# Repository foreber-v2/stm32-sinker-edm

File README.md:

# stm32-sinker-edm

# Open-Source Low-Cost Sinker EDM (STM32)

<p align="center">
  
</p>

<div align="center" style="text-align:center;">
  
  <br>
  <em>📱 Watch the full YouTube Short demo</em>
</div>

<br>

An ultra-low-cost, open-source Sinker Electrical Discharge Machining (EDM) prototype designed to make advanced subtractive manufacturing accessible. Built using mostly recycled components and standard locally-sourced parts.

---

## 🎥 Demo & Working Principle

<h2 align="center" style="text-align:center; border:none;">🎥 Demonstration & Results</h2>

<!-- FILA 1: VIDEOS -->
<table align="center" border="0" cellspacing="0" cellpadding="10" style="display:table; width:auto; margin:0 auto; border:none;">
  <tr>
    <td align="center" valign="bottom" style="text-align:center; border:none; background:none;">
      <b>📺 Full Demo</b><br>
      
    </td>
    <td align="center" valign="bottom" style="text-align:center; border:none; background:none;">
      <b>📱 Short Demo</b><br>
      
    </td>
  </tr>
</table>

<!-- FILA 2: FOTOS (ahora clicables, abren la imagen completa) -->
<table align="center" border="0" cellspacing="0" cellpadding="10" style="display:table; width:auto; margin:0 auto; border:none;">
  <tr>
    <td align="center" valign="top" style="text-align:center; border:none; background:none;">
      
      <br>
      <sub><i>Fig 1. Workpieces detail</i></sub>
    </td>
    <td align="center" valign="top" style="text-align:center; border:none; background:none;">
      
      <br>
      <sub><i>Fig 2. Surface finish</i></sub>
    </td>
  </tr>
</table>

---

## 📌 A. Project Overview

### What problem does it solve?
Advanced subtractive manufacturing—specifically Electrical Discharge Machining (EDM)—is traditionally prohibitively expensive, limiting access to high-precision hard-metal cutting in low-income regions, small workshops, and educational environments. This project tackles that barrier by creating an open-source, ultra-low-cost sinker EDM machine built from the ground up using mostly recycled and locally available components.

### What was built?
A complete prototype system consisting of:
* A custom **spark-generating power unit** handling up to 150VDC and delivering adjustable pulses up to ~40A.
* Real-time **pulse monitoring and sensing** using LM311 comparators, keeping a tight 60 µs pulse width (establishing a theoretical 16.6 kHz frequency ceiling).
* A mechanical linear axis driven by standard **NEMA 17 stepper motors** to control electrode feed.
* An **STM32 microcontroller** core running refactored, English-documented firmware.

### Current development status
* **Status:** Experimental prototype ("As-Is").
* **Testing Note:** The control logic has been refactored, but it must be rigorously tested dry (without high-voltage rails or high-power IGBT stages) before live deployment.
* **Philosophy:** *It cuts indeed.*

---

## 📑 Documentation Index

Explore the detailed technical documentation for each subsystem below:

* **[B. System Architecture](docs/architecture.md)** — Block diagrams, power electronics topology, control loop logic, and user interface layout.
* **[C. Hardware & Bill of Materials](docs/hardware.md)** — recycled component sourcing, and physical assembly insides.
* **[D. Firmware & Control Logic](docs/control.md)** — Keil uVision project structure, state machines, pulse-monitoring routines, and safety/fault handling.
* **[E. Experimental Results & Oscilloscope Captures](docs/experimental-results.md) (Coming Soon)** — Short/open-circuit waveforms, gate drive signals, current noise analysis, cutting tests, and limitations.
* **[F. Engineering Decisions & Trade-offs](docs/engineering-decisions.md) (Coming Soon)** — Sinker vs. Wire EDM choice, reusing telecom power supplies (-50VDC), opting for IGBTs with built-in flyback diodes, method of short/spark detection, and cost optimization.
* **[G. Future Improvements](docs/future-improvements.md) (Coming Soon)** — Fluid flushing systems, advanced instrumentation, closed-loop actuator speed optimization, and next-gen roadmap.

---

<p align="center">
  <a href="#stm32-sinker-edm">⬆️ Back to Top</a>
</p>

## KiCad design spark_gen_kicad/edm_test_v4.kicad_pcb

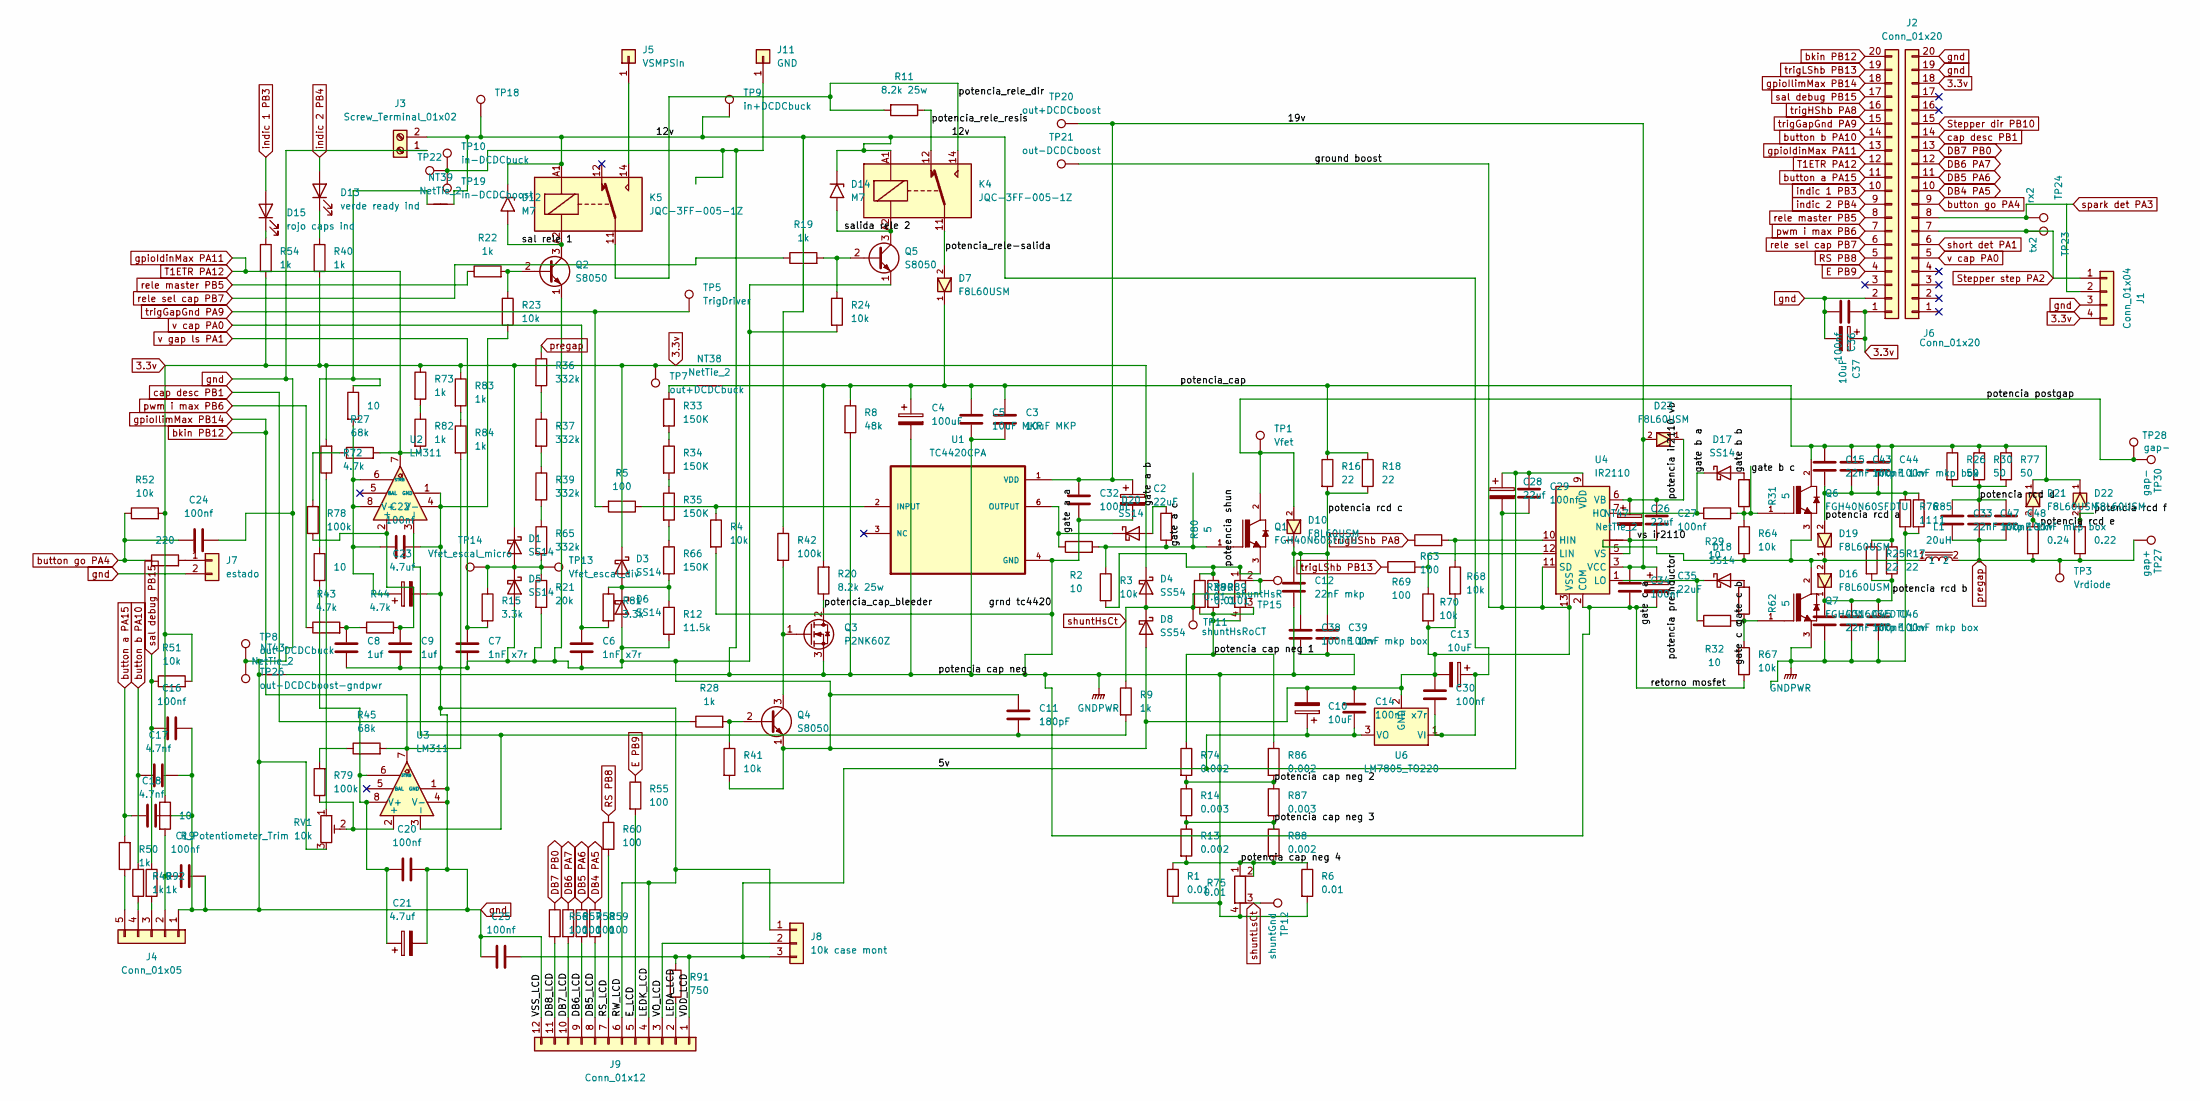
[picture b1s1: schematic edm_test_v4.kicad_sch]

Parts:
C2, C35: 22uF; CP_Radial_D5.0mm_P2.00mm
C3, C5: 10uF MKP; CP_Axial_L38.0mm_D21.0mm_P44.00mm_Horizontal
C4: 100uF; CP_Radial_D14.0mm_P7.50mm
C6, C7: 1nF x7r; C_Disc_D10.5mm_W5.0mm_P7.50mm
C8, C9: 1uf; C_1206_3216Metric_Pad1.33x1.80mm_HandSolder
C10, C13: 10uF; CP_Radial_D5.0mm_P2.50mm
C11: 180pF; C_Disc_D3.4mm_W2.1mm_P2.50mm
C12, C15, C31, C33: 22nF mkp; CP_Axial_L11.0mm_D6.0mm_P18.00mm_Horizontal
C14: 100nF x7r; C_0603_1608Metric_Pad1.08x0.95mm_HandSolder
C16, C19, C20, C22, C24, C25, C27, C29, C30, C32, C34, C36: 100nf; C_0603_1608Metric_Pad1.08x0.95mm_HandSolder
C17, C18: 4.7nf; C_0603_1608Metric_Pad1.08x0.95mm_HandSolder
C21, C23: 4.7uf; CP_Radial_D5.0mm_P2.50mm
C26, C28: 22uf; CP_Radial_D5.0mm_P2.50mm
C37: 10uF; CP_Radial_D5.0mm_P2.00mm
C38, C43, C45, C47: 100nF 1kv; C_Disc_D16.0mm_W5.0mm_P10.00mm
C39, C44, C46, C48: 100nF mkp box; C_Rect_L13.0mm_W6.0mm_P10.00mm_FKS3_FKP3_MKS4
D1, D3, D5, D6, D17, D18, D20: SS14; D_SMA
D4, D8: SS54; D_SMA
D7: F8L60USM; f8l60_c_disipador_incluido_techo
D10, D16, D19, D22, D23: F8L60USM; SOD113
D12, D14: M7; D_SMA
D13: verde ready ind; LED_D3.0mm_IRGrey
D15: rojo caps ind; LED_D3.0mm
D21: F8L60USM; f8l60_c_disipador_incluido
J1: Conn_01x04; PinSocket_1x04_P2.54mm_Vertical
J2, J6: Conn_01x20; PinSocket_1x20_P2.54mm_Vertical
J3: Screw_Terminal_01x02; TerminalBlock_MaiXu_MX126-5.0-02P_1x02_P5.00mm
J4: Conn_01x05; PinSocket_1x05_P2.54mm_Vertical
J5: VSMPSIn; TestPoint_2Pads_Pitch5.08mm_Drill1.3mm
J7: estado; PinSocket_1x02_P2.54mm_Vertical
J8: 10k case mont; PinSocket_1x03_P2.54mm_Vertical
J9: Conn_01x12; PinSocket_1x12_P2.54mm_Vertical
J11: GND; TestPoint_2Pads_Pitch5.08mm_Drill1.3mm
K4, K5: JQC-3FF-005-1Z; Relay_SPDT_Hongfa_JQC-3FF_0XX-1Z
L1: 20uH; L_Vertical_L75mm_D35mm_P85mm-uHcs270125e18X4
NT38, NT43, NT47: NetTie_2; NetTie-2_SMD_Pad2.0mm
NT39: NetTie_2
Q1: FGH40N60SFDTU; fgh40n60_c_disipador; PARTREV 2
Q2, Q4, Q5: S8050; TO-92_Inline
Q3: P2NK60Z; TO-220-3_Vertical
Q6: FGH40N60SFDTU; TO556P1587X482X2475-3; PARTREV 2
Q7: FGH40N60SFDTU; fgh40n60_c_disipador_y_diodo; PARTREV 2
R1, R6, R89, R90: 0.01; R_2512_6332Metric_Pad1.40x3.35mm_HandSolder
R2, R7, R10, R29, R32, R46: 10; R_1206_3216Metric_Pad1.30x1.75mm_HandSolder
R3, R51, R52, R64, R67: 10k; R_1206_3216Metric_Pad1.30x1.75mm_HandSolder
R4, R23, R24, R41, R68, R70: 10k; R_0805_2012Metric_Pad1.20x1.40mm_HandSolder
R5, R55: 100; R_1206_3216Metric_Pad1.30x1.75mm_HandSolder
R8: 48k; R_Axial_DIN0617_L17.0mm_D6.0mm_P5.08mm_Vertical
R9, R19, R22, R28, R40, R54, R73, R82, R83, R84: 1k; R_0805_2012Metric_Pad1.20x1.40mm_HandSolder
R11, R20: 8.2k 25w; R_Axial_Power_L60.0mm_W14.0mm_P66.04mm
R12: 11.5k; R_1206_3216Metric_Pad1.30x1.75mm_HandSolder
R13, R74, R86, R88: 0.002; R_2512_6332Metric_Pad1.40x3.35mm_HandSolder
R14, R87: 0.003; R_2512_6332Metric_Pad1.40x3.35mm_HandSolder
R15, R81: 3.3k; R_0805_2012Metric_Pad1.20x1.40mm_HandSolder
R16, R18: 22; R_Axial_DIN0516_L15.5mm_D5.0mm_P20.32mm_Horizontal
R17, R25: 22; R_Axial_DIN0414_L11.9mm_D4.5mm_P15.24mm_Horizontal
R21: 20k; R_1206_3216Metric_Pad1.30x1.75mm_HandSolder
R26, R30: 50; R_Axial_DIN0516_L15.5mm_D5.0mm_P20.32mm_Horizontal
R27, R45: 68k; R_2010_5025Metric_Pad1.40x2.65mm_HandSolder
R31, R62, R80: 5; R_1206_3216Metric_Pad1.30x1.75mm_HandSolder
R33, R34, R35, R66: 150K; R_1206_3216Metric_Pad1.30x1.75mm_HandSolder
R36, R37, R39, R65: 332k; R_1206_3216Metric_Pad1.30x1.75mm_HandSolder
R38: 0.01; R_Shunt_Vishay_WSK2512_6332Metric_T2.21mm
R42, R78, R79: 100k; R_1206_3216Metric_Pad1.30x1.75mm_HandSolder
R43, R44, R72: 4.7k; R_0805_2012Metric_Pad1.20x1.40mm_HandSolder
R49, R50, R92: 1k; R_1206_3216Metric_Pad1.30x1.75mm_HandSolder
R53: 220; R_Axial_DIN0204_L3.6mm_D1.6mm_P5.08mm_Horizontal
R56: 100; R_Axial_DIN0204_L3.6mm_D1.6mm_P7.62mm_Horizontal
R57, R58, R59, R60: 100; R_Axial_DIN0207_L6.3mm_D2.5mm_P10.16mm_Horizontal
R61: 0.24; R_Axial_DIN0516_L15.5mm_D5.0mm_P20.32mm_Horizontal
R63, R69: 100; R_0805_2012Metric_Pad1.20x1.40mm_HandSolder
R71: 0.22; R_Axial_DIN0516_L15.5mm_D5.0mm_P20.32mm_Horizontal
R75: 0.01; R_Shunt_Vishay_WSK2512_6332Metric_T2.66mm
R76, R85: 11; R_Axial_DIN0617_L17.0mm_D6.0mm_P25.40mm_Horizontal
R77: 50; R_Axial_DIN0617_L17.0mm_D6.0mm_P25.40mm_Horizontal
R91: 750; R_0805_2012Metric_Pad1.20x1.40mm_HandSolder
RV1: R_Potentiometer_Trim 10k; Potentiometer_Bourns_3296W_Vertical
TP1: Vfet; TestPoint_Keystone_5005-5009_Compact
TP3: Vrdiode; TestPoint_Keystone_5005-5009_Compact
TP5: TrigDriver; TestPoint_Keystone_5005-5009_Compact
TP7: out+DCDCbuck; TestPoint_Keystone_5005-5009_Compact
TP8: out-DCDCbuck; TestPoint_Keystone_5005-5009_Compact
TP9: in+DCDCbuck; TestPoint_Keystone_5005-5009_Compact
TP10: in-DCDCbuck; TestPoint_Keystone_5005-5009_Compact
TP11: shuntHsRoCT; TestPoint_Keystone_5005-5009_Compact
TP12: shuntGnd; TestPoint_Keystone_5000-5004_Miniature
TP13: Vfet_escal_div; TestPoint_Keystone_5005-5009_Compact
TP14: Vfet_escal_micro; TestPoint_Keystone_5000-5004_Miniature
TP15: shuntHsR; TestPoint_Keystone_5005-5009_Compact
TP18: in+DCDCboost; TestPoint_Keystone_5005-5009_Compact
TP19: in-DCDCboost; TestPoint_Keystone_5005-5009_Compact
TP20: out+DCDCboost; TestPoint_Keystone_5005-5009_Compact
TP21: out-DCDCboost; TestPoint_Keystone_5005-5009_Compact
TP22: guard; TestPoint_THTPad_1.5x1.5mm_Drill0.7mm
TP23: tx2; TestPoint_Keystone_5005-5009_Compact
TP24: rx2; TestPoint_Keystone_5005-5009_Compact
TP26: out-DCDCboost-gndpwr; TestPoint_Keystone_5005-5009_Compact
TP27: gap+; TestPoint_Keystone_5005-5009_Compact
TP28, TP30: gap-; TestPoint_Keystone_5005-5009_Compact
U1: TC4420CPA; DIP787W46P254L927H533Q8
U2, U3: LM311; DIP794W45P254L959H508Q8
U4: IR2110; DIP-14_W7.62mm
U6: LM7805_TO220; TO-220-3_Vertical

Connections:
3.3v: C36.1, C37.1, D1.1 (K), D3.1 (K), D4.1 (K), J1.4, J2.18, J6.1, R7.1, R40.2, R51.2, R52.2, R54.2, R72.2, R73.1, R83.1, TP7.1 (1_1)
/5v: C10.1, C14.1, C25.1, C28.1, C29.1, J8.3, J9.1, R91.1, U4.9 (VDD), U6.3 (VO)
/12v: C13.1, C30.2, D12.1 (A1), D14.1 (A1), J3.2, K4.A1, K5.A1, NT39.2, R42.1, TP9.1 (1_1), TP18.1 (1_1), U6.1 (VI)
/DB5_LCD: J9.8, R59.2
/DB6_LCD: J9.9, R58.2
/DB7_LCD: J9.10, R57.2
/DB8_LCD: J9.11, R56.2
/E_LCD: J9.5, R55.2
/LEDA_LCD: J9.2, R91.2
/RS_LCD: J9.7, R60.2
/VO_LCD: J8.2, J9.3
/gate a a: D20.1 (K), R2.1, U1.6 (OUTPUT), U1.7 (OUTPUT)
/gate a b: D20.2 (A), R80.2
/gate a c: Q1.1, R2.2, R3.1, R80.1
/gate b a: D17.1 (K), R29.1, U4.7 (HO)
/gate b b: D17.2 (A), R31.2
/gate b c: Q6.1, R29.2, R31.1, R64.1
/gate c a: D18.1 (K), R32.1, U4.1 (LO)
/gate c b: D18.2 (A), R62.2
/gate c c: Q7.1, R32.2, R62.1, R67.1
/poteencia shun: Q1.3, R3.2, R38.1, R89.1, R90.1
/potencia cap neg 1: R38.3, R38.4, R74.1, R86.1, R89.2, R90.2
/potencia cap neg 2: R14.1, R74.2, R86.2, R87.1
/potencia cap neg 3: R13.1, R14.2, R87.2, R88.1
/potencia cap neg 4: R1.1, R6.1, R13.2, R75.1, R75.2, R88.2
/potencia ir2110 vb: C26.1, C27.1, D23.1, U4.6 (VB)
/potencia postgap: D10.2, Q1.2, TP1.1 (1_1), TP28.1 (1_1), TP30.1 (1_1)
/potencia preinductor: D16.2, D19.1, L1.1, NT47.2, Q6.3, Q7.2, R64.2
/potencia rcd a: C15.1, C43.1, C44.1, D19.2, R76.1, R85.1
/potencia rcd b: C31.2, C45.2, C46.2, D16.1, R17.2, R25.2
/potencia rcd c: C12.2, C38.2, C39.2, D10.1, R16.2, R18.2
/potencia rcd d: C33.2, C47.2, C48.2, R26.2, R30.2, R77.2
/potencia rcd e: D21.2, R61.1
/potencia rcd f: D22.2, R71.1
/potencia_cap: C3.1, C4.1, C5.1, C15.2, C43.2, C44.2, D7.1, D21.1, D22.1, NT38.1, Q6.2, R8.1, R16.1, R17.1, R18.1, R20.2, R25.1, R26.1, R30.1, R77.1
/potencia_cap_bleeder: Q3.2 (D), R20.1
/potencia_rele-salida: D7.2, K4.11
/potencia_rele_dir: K4.14, K5.11, R11.2
/potencia_rele_resis: K4.12, R11.1
/sal rele 1: D12.2 (A2), K5.A2, Q2.3 (C)
/salida rele 2: D14.2 (A2), K4.A2, Q5.3 (C)
/vs ir2110: C26.2, C27.2, NT47.1, U4.5 (VS)
DB4 PA5: J2.10, R59.1
DB5 PA6: J2.11, R58.1
DB6 PA7: J2.12, R57.1
DB7 PB0: J2.13, R56.1
E PB9: J6.4, R55.1
GNDPWR: C2.2, C3.2, C4.2, C5.2, C12.1, C31.1, C32.2, C34.2, C35.2, C38.1, C39.1, C45.1, C46.1, J11.1 (Pin_1_1), NT43.1, Q3.3 (S), Q7.3, R1.2, R4.2, R6.2, R8.2, R67.2, R75.4, R76.2, R85.2, TP10.1 (1_1), TP19.1 (1_1), TP22.1 (1_1), U1.4 (GND), U1.5 (GND), U4.2 (COM)
unnamed: C8.2, R43.2, R44.1
unnamed: D1.2 (A), D5.1 (K), R15.1, R21.1, R65.2, TP13.1 (1_1), TP14.1 (1_1)
unnamed: D3.2 (A), D6.1 (K), R12.1, R66.2, R81.1
unnamed: D13.1 (K), R40.1
unnamed: D15.1 (K), R54.1
unnamed: C19.2, J4.2, R7.2
unnamed: J4.3, R92.2
unnamed: J4.4, R49.1
unnamed: J4.5, R50.1
unnamed: J5.1 (Pin_1_1), K5.14
unnamed: J7.1, R53.2
unnamed: NT38.2, R33.1
unnamed: NT39.1, R10.1, R46.1
unnamed: Q2.2 (B), R22.2, R23.1
unnamed: Q3.1 (G), Q4.3 (C), R42.2
unnamed: Q4.2 (B), R28.2, R41.1
unnamed: Q5.2 (B), R19.2, R24.1
unnamed: R27.1, R78.2
unnamed: R33.2, R34.1
unnamed: R34.2, R35.1
unnamed: R35.2, R66.1
unnamed: R36.2, R37.1
unnamed: R37.2, R39.1
unnamed: R39.2, R65.1
unnamed: R45.1, R79.2
unnamed: R72.1, RV1.1
unnamed: R73.2, R82.1
unnamed: R83.2, R84.1
unnamed: R4.1, R5.1, U1.2 (INPUT)
unnamed: C9.2, R44.2, R78.1, U2.2 (+)
unnamed: C11.1, R9.2, U2.3 (-), U3.3 (-)
unnamed: C22.2, C23.1, R10.2, U2.6 (STRB), U2.8 (V+)
unnamed: R79.1, RV1.2, U3.2 (+)
unnamed: C20.2, C21.1, R46.2, U3.6 (STRB), U3.8 (V+)
unnamed: R63.2, R68.1, U4.10 (HIN)
unnamed: R69.2, R70.1, U4.12 (LIN)
RS PB8: J6.5, R60.1
Stepper dir PB10: J2.15
Stepper step PA2: J1.1, J2.7, TP23.1 (1_1)
T1ETR PA12: J6.12, J6.13, R27.2, R82.2, U2.7
VDD: C2.1, C32.1, C34.1, C35.1, D23.2, TP20.1 (1_1), U1.1 (VDD), U1.8 (VDD), U4.3 (VCC)
bkin PB12: J6.18, J6.20, R45.2, R84.2, U3.7
button a PA15: C18.2, J6.11, R50.2
button b PA10: C17.2, J6.14, R49.2
button go PA4: C24.2, J2.9, R52.1, R53.1
cap desc PB1: J2.14, R28.1
gnd: C6.1, C7.1, C8.1, C9.1, C10.2, C11.2, C13.2, C14.2, C16.1, C17.1, C18.1, C19.1, C20.1, C21.2, C22.1, C23.2, C24.1, C25.2, C28.2, C29.2, C30.1, C36.2, C37.2, D5.2 (A), D6.2 (A), D8.2 (A), J1.3, J2.19, J2.20, J3.1, J4.1, J6.2, J7.2, J8.1, J9.4, J9.6, J9.12, NT43.2, Q2.1 (E), Q4.1 (E), Q5.1 (E), R12.2, R21.2, R23.2, R24.2, R41.2, R68.2, R70.2, RV1.3, TP8.1 (1_1), TP21.1 (1_1), TP26.1 (1_1), U2.1 (GND), U2.4 (V-), U3.1 (GND), U3.4 (V-), U4.11 (SD), U4.13 (VSS), U6.2 (GND)
indic 1 PB3: D15.2 (A), J6.10
indic 2 PB4: D13.2 (A), J6.9
pregap: C33.1, C47.1, C48.1, L1.2, R36.1, R61.2, R71.2, TP3.1 (1_1), TP27.1 (1_1)
pwm i max PB6: J6.7, R43.1
rele master PB5: J6.8, R22.1
rele sel cap PB7: J6.6, R19.1
sal debug PB15: C16.2, J6.17, R51.1, R92.1
short det PA1: J2.6
shuntHsCt: D4.2 (A), D8.1 (K), R9.1, R38.2, TP11.1 (1_1), TP15.1 (1_1)
shuntLsCt: R75.3, TP12.1 (1_1)
spark det PA3: J2.8, TP24.1 (1_1)
trigGapGnd PA9: J6.15, R5.2, TP5.1 (1_1)
trigHShb PA8: J6.16, R63.1
trigLShb PB13: J6.19, R69.1
v cap PA0: C6.2, J2.5, R81.2
v gap ls PA1: C7.2, R15.2

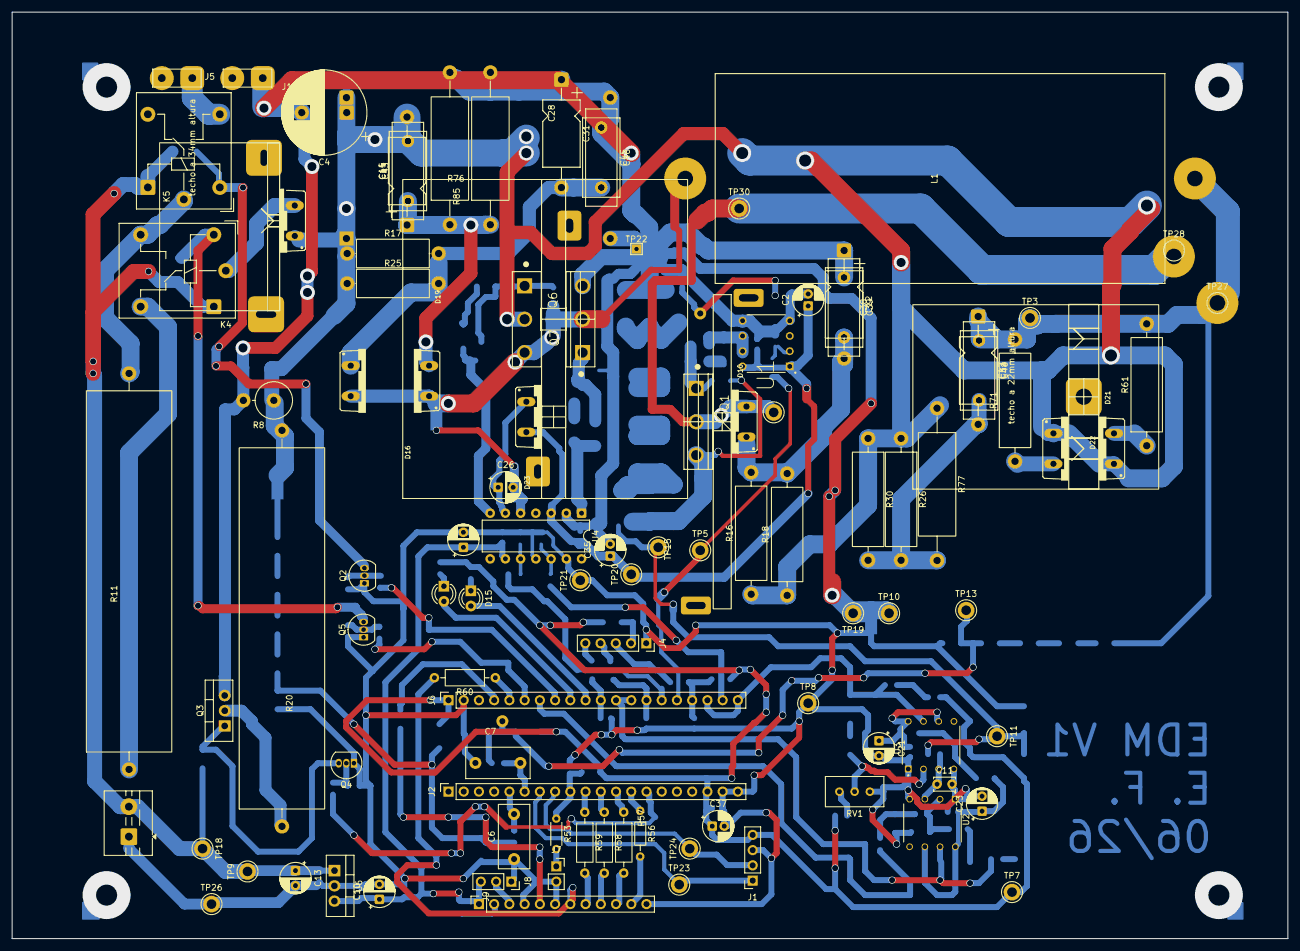
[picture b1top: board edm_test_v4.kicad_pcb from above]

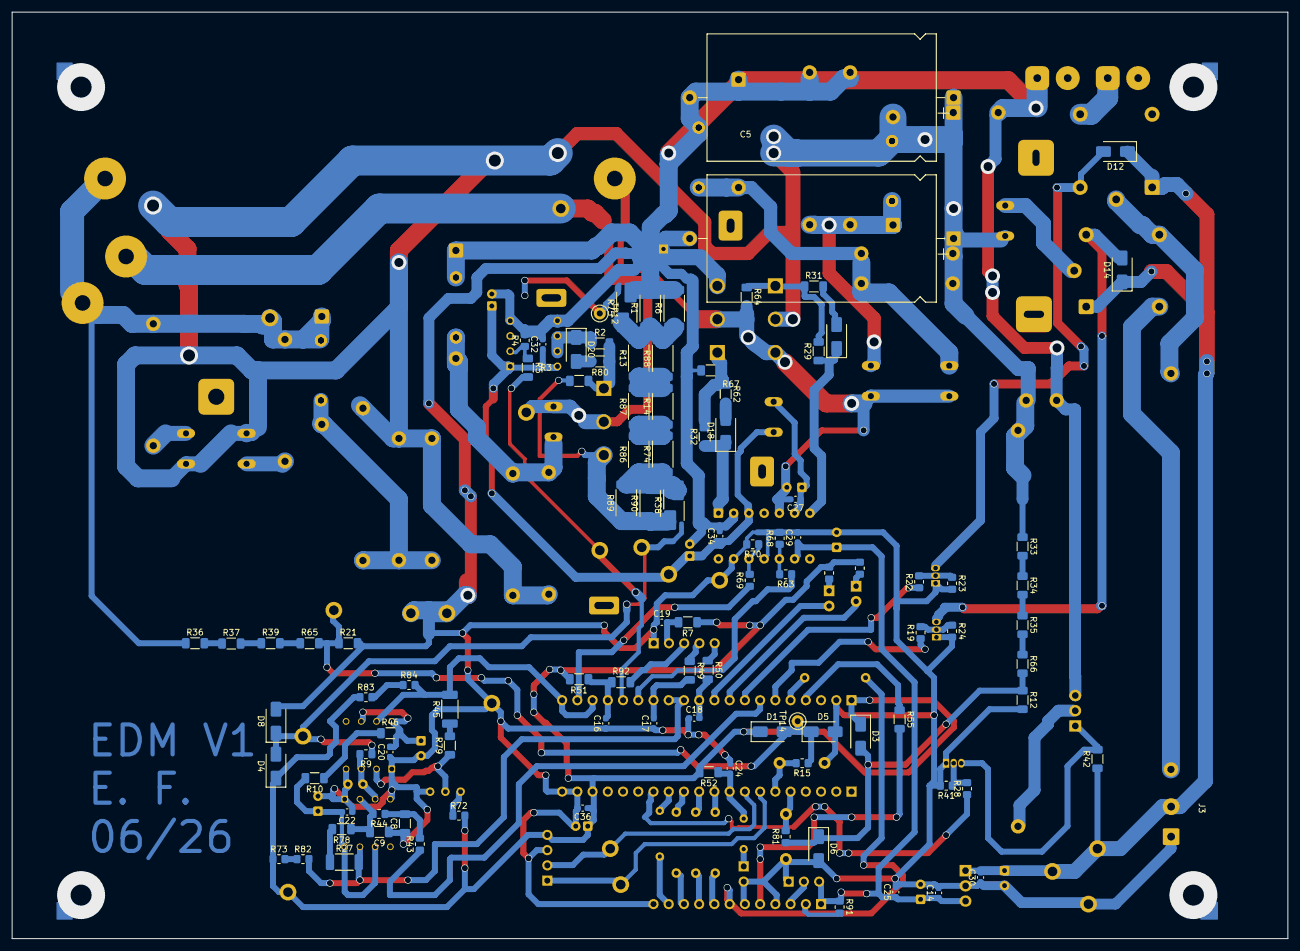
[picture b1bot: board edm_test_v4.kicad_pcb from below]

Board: 2 copper layers, 212.8 x 154.5 mm, 206 parts (105 on the bottom side), 109 nets.

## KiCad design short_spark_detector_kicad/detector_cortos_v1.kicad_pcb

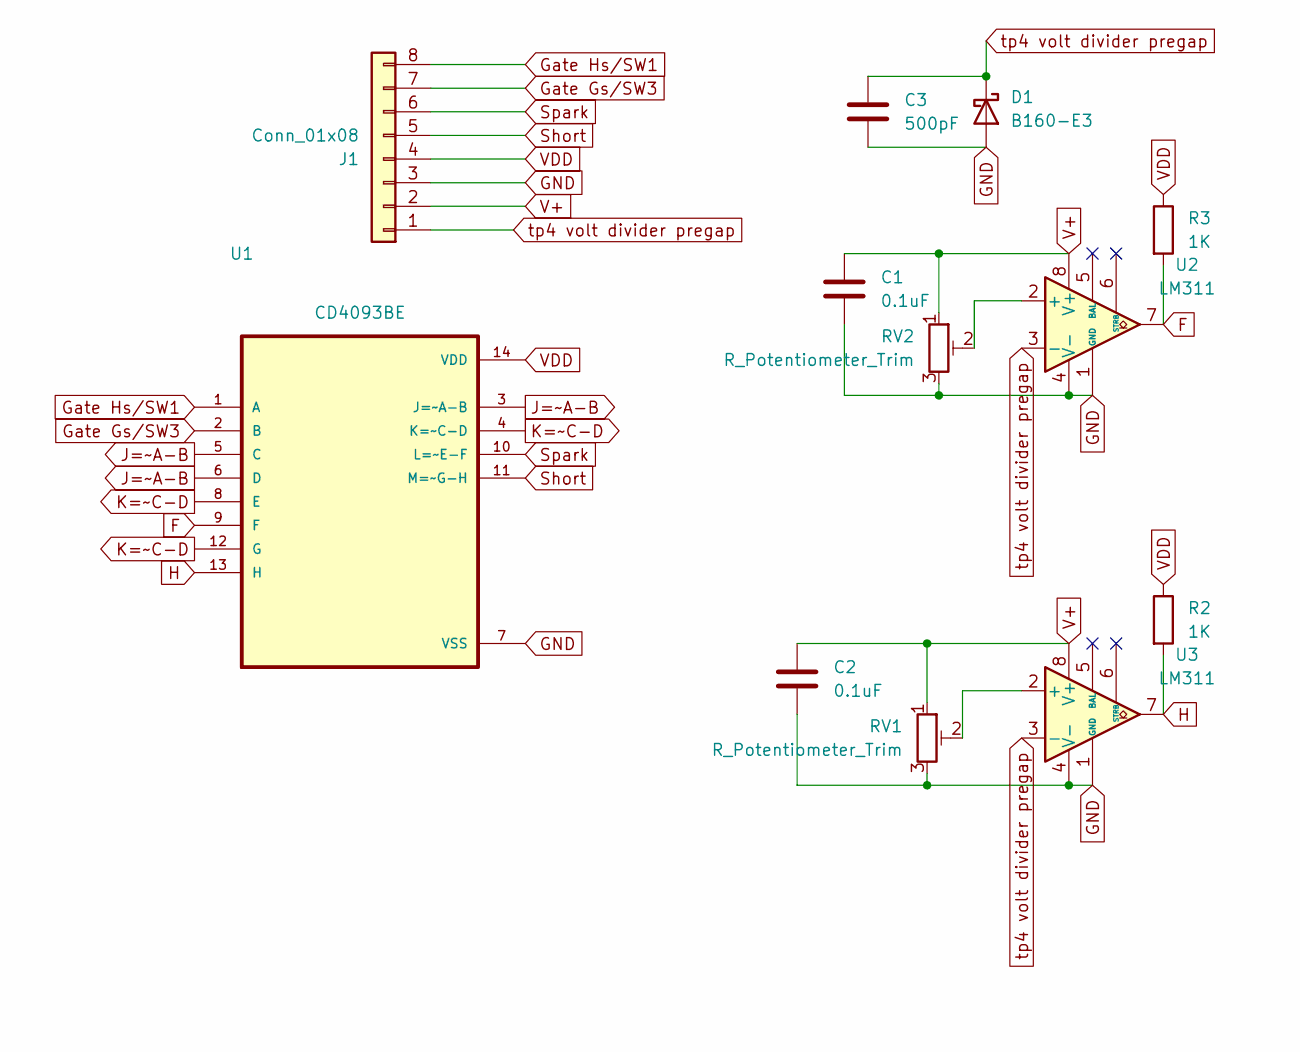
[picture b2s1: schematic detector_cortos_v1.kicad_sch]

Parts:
C1, C2: 0.1uF; C_Disc_D10.0mm_W2.5mm_P5.00mm
C3: 500pF; C_Disc_D10.0mm_W2.5mm_P5.00mm
D1: B160-E3; D_SMA
J1: Conn_01x08; PinHeader_1x08_P2.54mm_Vertical
R2, R3: 1K; R_Axial_DIN0207_L6.3mm_D2.5mm_P7.62mm_Horizontal
RV1, RV2: R_Potentiometer_Trim; Potentiometer_Vishay_T93YA_Vertical
U1: CD4093BE; DIP794W45P254L1969H508Q14; DigiKey_Part_Number 296-2068-5-ND
U2, U3: LM311; DIP794W45P254L959H508Q8

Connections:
F: R3.2, U1.9 (F), U2.7
GND: C1.2, C2.2, C3.2, D1.2 (A), J1.3, RV1.3, RV2.3, U1.7 (VSS), U2.1 (GND), U2.4 (V-), U3.1 (GND), U3.4 (V-)
Gate Gs/SW3: J1.7, U1.2 (B)
Gate Hs/SW1: J1.8, U1.1 (A)
H: R2.2, U1.13 (H), U3.7
J=~A-B: U1.3 (J=~A-B), U1.5 (C), U1.6 (D)
K=~C-D: U1.4 (K=~C-D), U1.8 (E), U1.12 (G)
unnamed: RV2.2, U2.2 (+)
unnamed: RV1.2, U3.2 (+)
Short: J1.5, U1.11 (M=~G-H)
Spark: J1.6, U1.10 (L=~E-F)
V+: C1.1, C2.1, J1.2, RV1.1, RV2.1, U2.8 (V+), U3.8 (V+)
VDD: J1.4, R2.1, R3.1, U1.14 (VDD)
tp4 volt divider pregap: C3.1, D1.1 (K), J1.1, U2.3 (-), U3.3 (-)

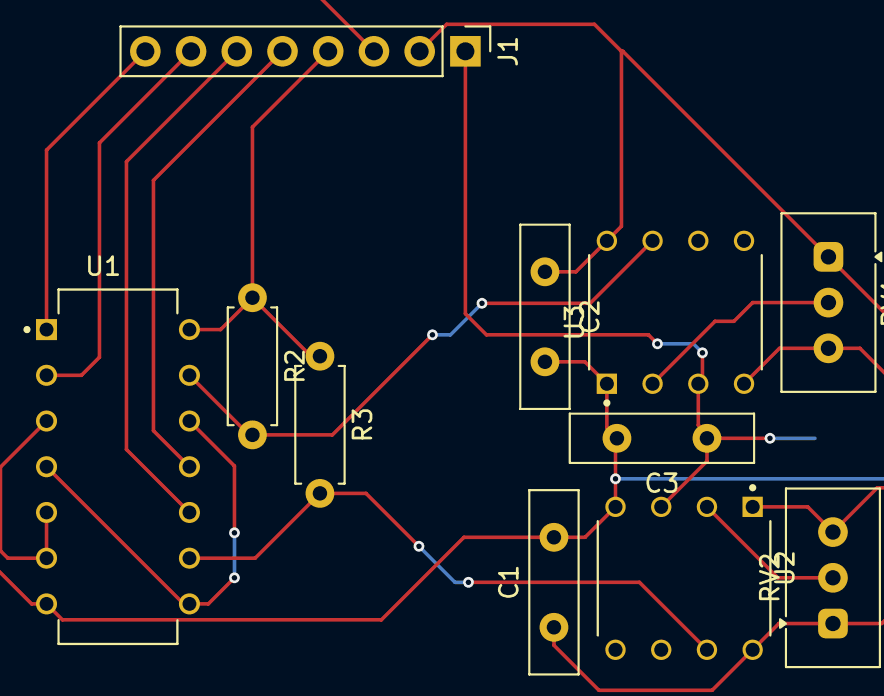
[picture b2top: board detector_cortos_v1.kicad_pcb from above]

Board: 2 copper layers, 12 parts (1 on the bottom side), 14 nets.
